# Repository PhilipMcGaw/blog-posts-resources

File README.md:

# Blog Post Resources

This repo is contains

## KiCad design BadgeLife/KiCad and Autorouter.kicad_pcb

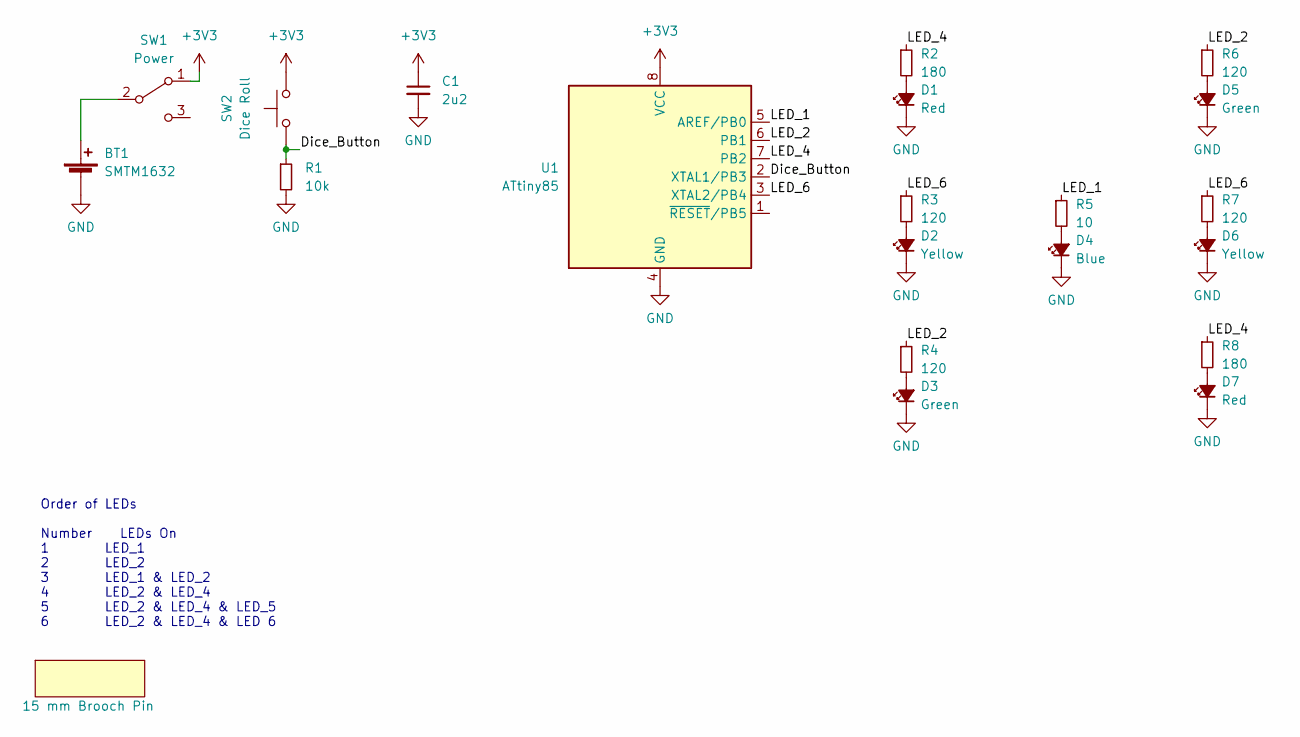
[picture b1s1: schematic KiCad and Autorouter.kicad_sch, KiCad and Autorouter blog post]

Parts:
BT1: SMTM1632; Mouser Part Number 614-SMTM1632
C1: 2u2; C_1206_3216Metric_Pad1.33x1.80mm_HandSolder
D1, D7: Red; D_0805_2012Metric_Pad1.15x1.40mm_HandSolder
D2, D6: Yellow; D_1206_3216Metric_Pad1.42x1.75mm_HandSolder
D3, D5: Green; D_0603_1608Metric_Pad1.05x0.95mm_HandSolder
D4: Blue; D_0402_1005Metric_Pad0.77x0.64mm_HandSolder
Pin1: 15 mm Brooch Pin
R1: 10k; R_1206_3216Metric_Pad1.30x1.75mm_HandSolder
R2, R8: 180; R_0805_2012Metric_Pad1.20x1.40mm_HandSolder
R3, R7: 120; R_1206_3216Metric_Pad1.30x1.75mm_HandSolder
R4, R6: 120; R_0603_1608Metric_Pad0.98x0.95mm_HandSolder
R5: 10; R_0402_1005Metric_Pad0.72x0.64mm_HandSolder
SW1: Power; SW_SPDT_PCM12
SW2: Dice Roll; SW_Push_1P1T_NO_CK_KMR2
U1: ATtiny85; SOIC-8W_5.3x5.3mm_P1.27mm

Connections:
+3V3: C1.1, SW1.1 (A), SW2.2, U1.8 (VCC)
/Dice_Button: R1.1, SW2.1, U1.2 (XTAL1/PB3)
/LED_1: R5.1, U1.5 (AREF/PB0)
/LED_2: R4.1, R6.1, U1.6 (PB1)
/LED_4: R2.1, R8.1, U1.7 (PB2)
/LED_6: R3.1, R7.1, U1.3 (XTAL2/PB4)
GND: BT1.2 (-), C1.2, D1.1 (K), D2.1 (K), D3.1 (K), D4.1 (K), D5.1 (K), D6.1 (K), D7.1 (K), R1.2, U1.4 (GND)
unnamed: BT1.1 (+), SW1.2 (B)
unnamed: D1.2 (A), R2.2
unnamed: D2.2 (A), R3.2
unnamed: D3.2 (A), R4.2
unnamed: D4.2 (A), R5.2
unnamed: D5.2 (A), R6.2
unnamed: D6.2 (A), R7.2
unnamed: D7.2 (A), R8.2

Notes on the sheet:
Order of LEDs Number LEDs On 1 LED_1 2 LED_2 3 LED_1 & LED_2 4 LED_2 & LED_4 5 LED_2 & LED_4 & LED_5 6 LED_2 & LED_4 & LED 6

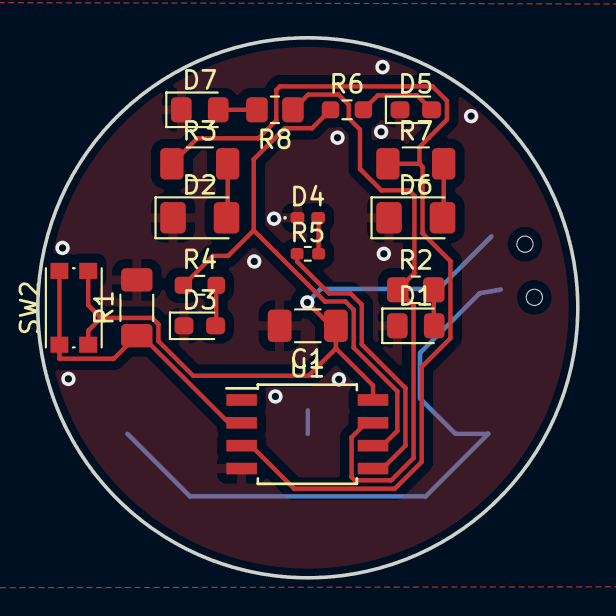
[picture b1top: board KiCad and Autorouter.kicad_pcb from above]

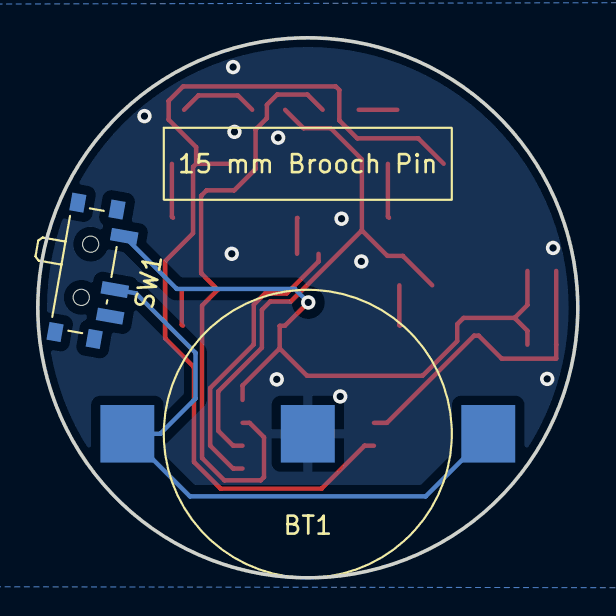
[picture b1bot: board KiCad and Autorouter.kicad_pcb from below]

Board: 2 copper layers, 30.0 x 30.0 mm, 21 parts (3 on the bottom side), 15 nets.

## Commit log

2022-06-26 Schematic Drawn and PCB Routed
2022-06-26 moved files
2022-06-26 HtmlBom Generated and one footprint corrected
2022-06-26 Added more resource files
2022-06-27 more small edits
